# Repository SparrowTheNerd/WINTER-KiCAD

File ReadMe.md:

WINTER Revision 3.3 Board and Production Files. Legacy as of Aug 28, 2025

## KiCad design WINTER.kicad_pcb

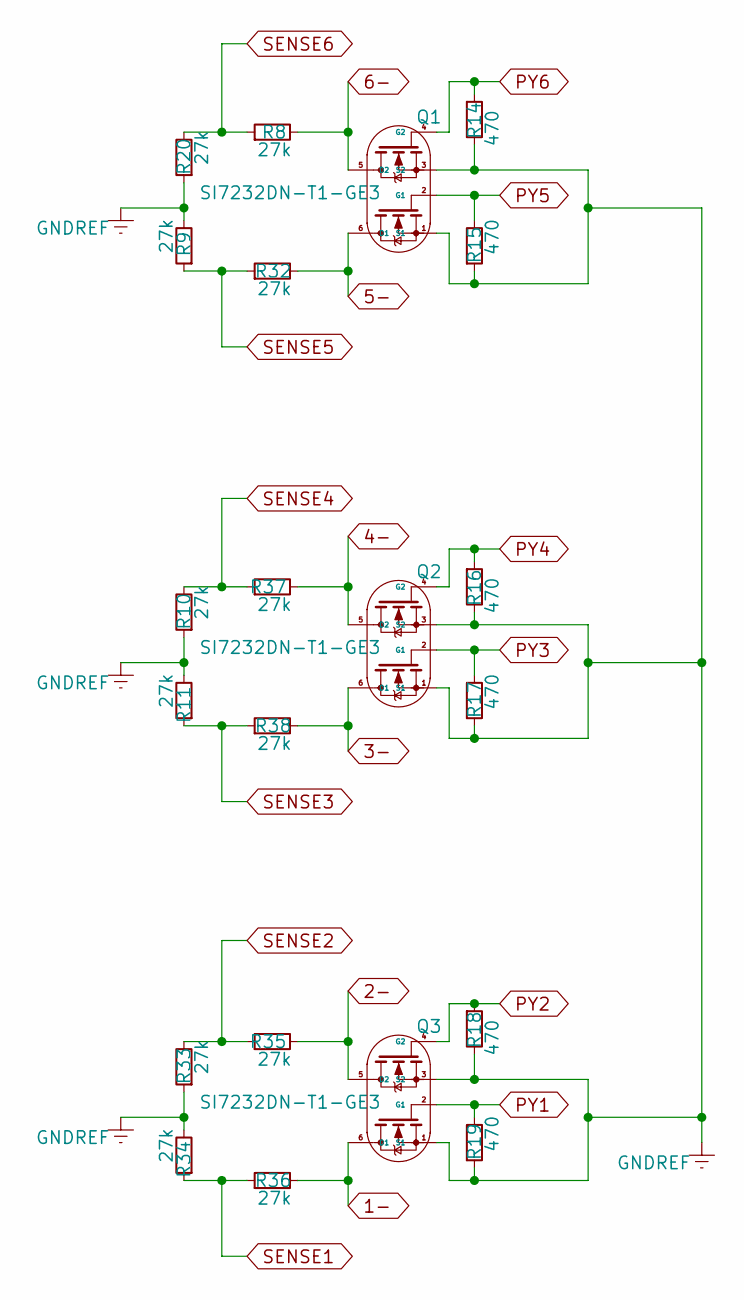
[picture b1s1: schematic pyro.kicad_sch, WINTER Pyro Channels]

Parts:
Q1, Q2, Q3: SI7232DN-T1-GE3; TRANS_SI7232DN-T1-GE3; LCSC C144854
R8, R32, R35, R36, R37, R38: 27k; R_0603_1608Metric; LCSC C22967
R9, R10, R11, R20, R33, R34: 27k; R_0603_1608Metric; LCSC C25803
R14, R15, R16, R17, R18, R19: 470; R_0603_1608Metric; LCSC C23179

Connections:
1-: Q3.6 (D1), R36.2; also elsewhere on the board
2-: Q3.5 (D2), R35.2; also elsewhere on the board
3-: Q2.6 (D1), R38.2; also elsewhere on the board
4-: Q2.5 (D2), R37.2; also elsewhere on the board
5-: Q1.6 (D1), R32.2; also elsewhere on the board
6-: Q1.5 (D2), R8.2; also elsewhere on the board
GNDREF: Q1.1 (S1), Q1.3 (S2), Q2.1 (S1), Q2.3 (S2), Q3.1 (S1), Q3.3 (S2), R9.2, R10.1, R11.2, R14.2, R15.1, R16.2, R17.1, R18.2, R19.1, R20.1, R33.1, R34.2; also elsewhere on the board
PY1: Q3.2 (G1), R19.2; also elsewhere on the board
PY2: Q3.4 (G2), R18.1; also elsewhere on the board
PY3: Q2.2 (G1), R17.2; also elsewhere on the board
PY4: Q2.4 (G2), R16.1; also elsewhere on the board
PY5: Q1.2 (G1), R15.2; also elsewhere on the board
PY6: Q1.4 (G2), R14.1; also elsewhere on the board
SENSE1: R34.1, R36.1; also elsewhere on the board
SENSE2: R33.2, R35.1; also elsewhere on the board
SENSE3: R11.1, R38.1; also elsewhere on the board
SENSE4: R10.2, R37.1; also elsewhere on the board
SENSE5: R9.1, R32.1; also elsewhere on the board
SENSE6: R8.1, R20.2; also elsewhere on the board

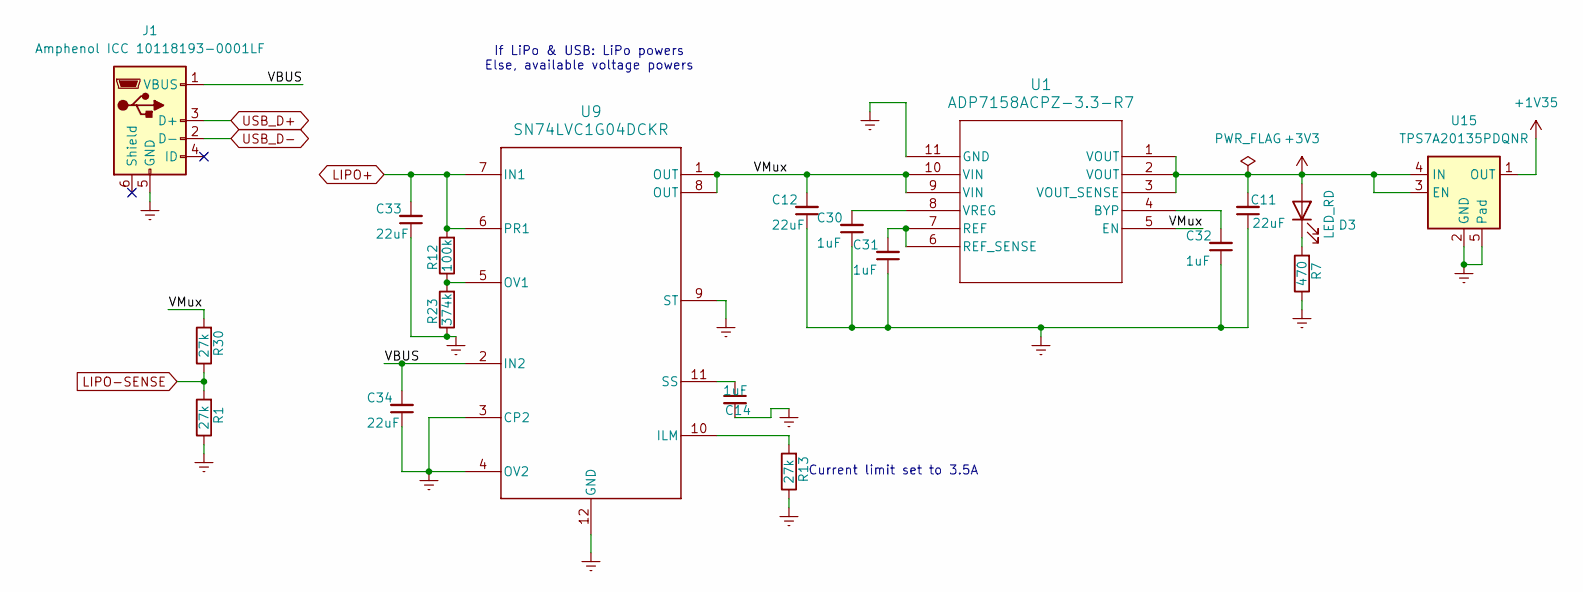
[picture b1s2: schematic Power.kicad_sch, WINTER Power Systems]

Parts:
C11, C12, C33, C34: 22uF; C_0603_1608Metric; LCSC C96446
C14: 1uF; C_0603_1608Metric; LCSC C1525
C30, C31, C32: 1uF; C_0603_1608Metric; LCSC C96446
D3: LED_RD; LED_0603_1608Metric; LCSC C2286
J1: Amphenol ICC 10118193-0001LF; USB_Micro-B_Amphenol_10118193-0001LF_Horizontal; LCSC C132562
R1, R13, R30: 27k; R_0603_1608Metric; LCSC C22967
R7: 470; R_0603_1608Metric; LCSC C23179
R12: 100k; R_0603_1608Metric; LCSC C23162
R23: 374k; R_0603_1608Metric
U1: ADP7158ACPZ-3.3-R7; CP-10-9_ADI
U9: SN74LVC1G04DCKR; RUX0012A
U15: TPS7A20135PDQNR; Texas_X2SON-4_1x1mm_P0.65mm

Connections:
+1V35: U15.1 (OUT); also elsewhere on the board
+3V3: C11.2, D3.2 (A), U1.1 (VOUT), U1.2 (VOUT), U1.3 (VOUT_SENSE), U15.3 (EN), U15.4 (IN); also elsewhere on the board
/Power/VBUS: C34.2, J1.1 (VBUS), U9.2 (IN2)
/Power/VMux: C12.2, R30.2, U1.5 (EN), U1.9 (VIN), U1.10 (VIN), U9.1 (OUT), U9.8 (OUT)
GNDREF: C11.1, C12.1, C14.2, C30.1, C31.1, C32.1, C33.1, C34.1, J1.5 (GND), R1.1, R7.1, R13.1, R23.1, U1.11 (GND), U9.3 (CP2), U9.4 (OV2), U9.9 (ST), U9.12 (GND), U15.2 (GND), U15.5 (Pad); also elsewhere on the board
LIPO+: C33.2, R12.2, U9.6 (PR1), U9.7 (IN1); also elsewhere on the board
LIPO-SENSE: R1.2, R30.1; also elsewhere on the board
unnamed: D3.1 (K), R7.2
unnamed: C32.2, U1.4 (BYP)
unnamed: C31.2, U1.6 (REF_SENSE), U1.7 (REF)
unnamed: C30.2, U1.8 (VREG)
unnamed: R13.2, U9.10 (ILM)
unnamed: R12.1, R23.2, U9.5 (OV1)
unnamed: C14.1, U9.11 (SS)
USB_D+: J1.3 (D+); also elsewhere on the board
USB_D-: J1.2 (D-); also elsewhere on the board

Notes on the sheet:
If LiPo & USB: LiPo powers Else, available voltage powers
Current limit set to 3.5A

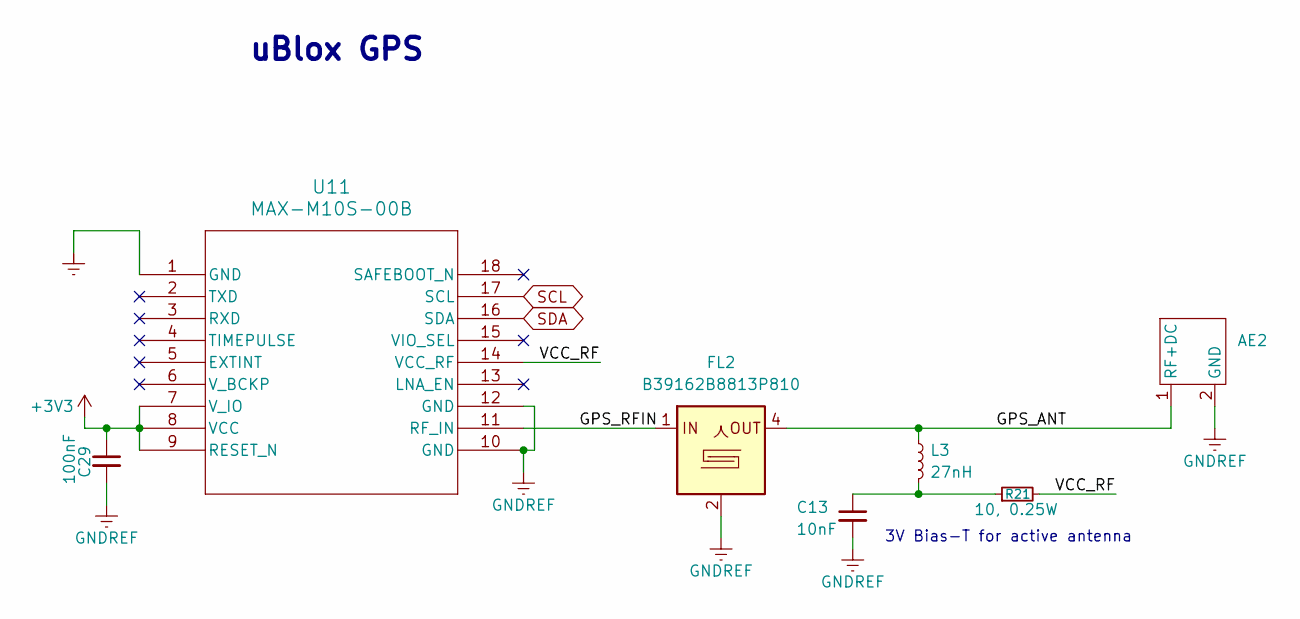
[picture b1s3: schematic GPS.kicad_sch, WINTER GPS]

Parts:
AE2: AP.10H.01
C13: 10nF; C_0603_1608Metric
C29: 100nF; C_0603_1608Metric; LCSC C1590
FL2: B39162B8813P810; Filter_1109-5_1.1x0.9mm
L3: 27nH; L_0402_1005Metric
R21: 10, 0.25W; R_0603_1608Metric
U11: MAX-M10S-00B; LCSC C4153167

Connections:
+3V3: C29.1, U11.7 (V_IO), U11.8 (VCC), U11.9 (RESET_N); also elsewhere on the board
/GPS/GPS_ANT: AE2.1 (RF+DC), FL2.4, L3.1
/GPS/GPS_RFIN: FL2.1, U11.11 (RF_IN)
/GPS/VCC_RF: R21.2, U11.14 (VCC_RF)
GNDREF: AE2.2 (GND), AE2.3 (GND), AE2.4 (GND), AE2.5 (GND), C13.2, C29.2, FL2.2, FL2.3, FL2.5, U11.1 (GND), U11.10 (GND), U11.12 (GND); also elsewhere on the board
unnamed: C13.1, L3.2, R21.1
SCL: U11.17 (SCL); also elsewhere on the board
SDA: U11.16 (SDA); also elsewhere on the board

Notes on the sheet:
uBlox GPS
3V Bias-T for active antenna

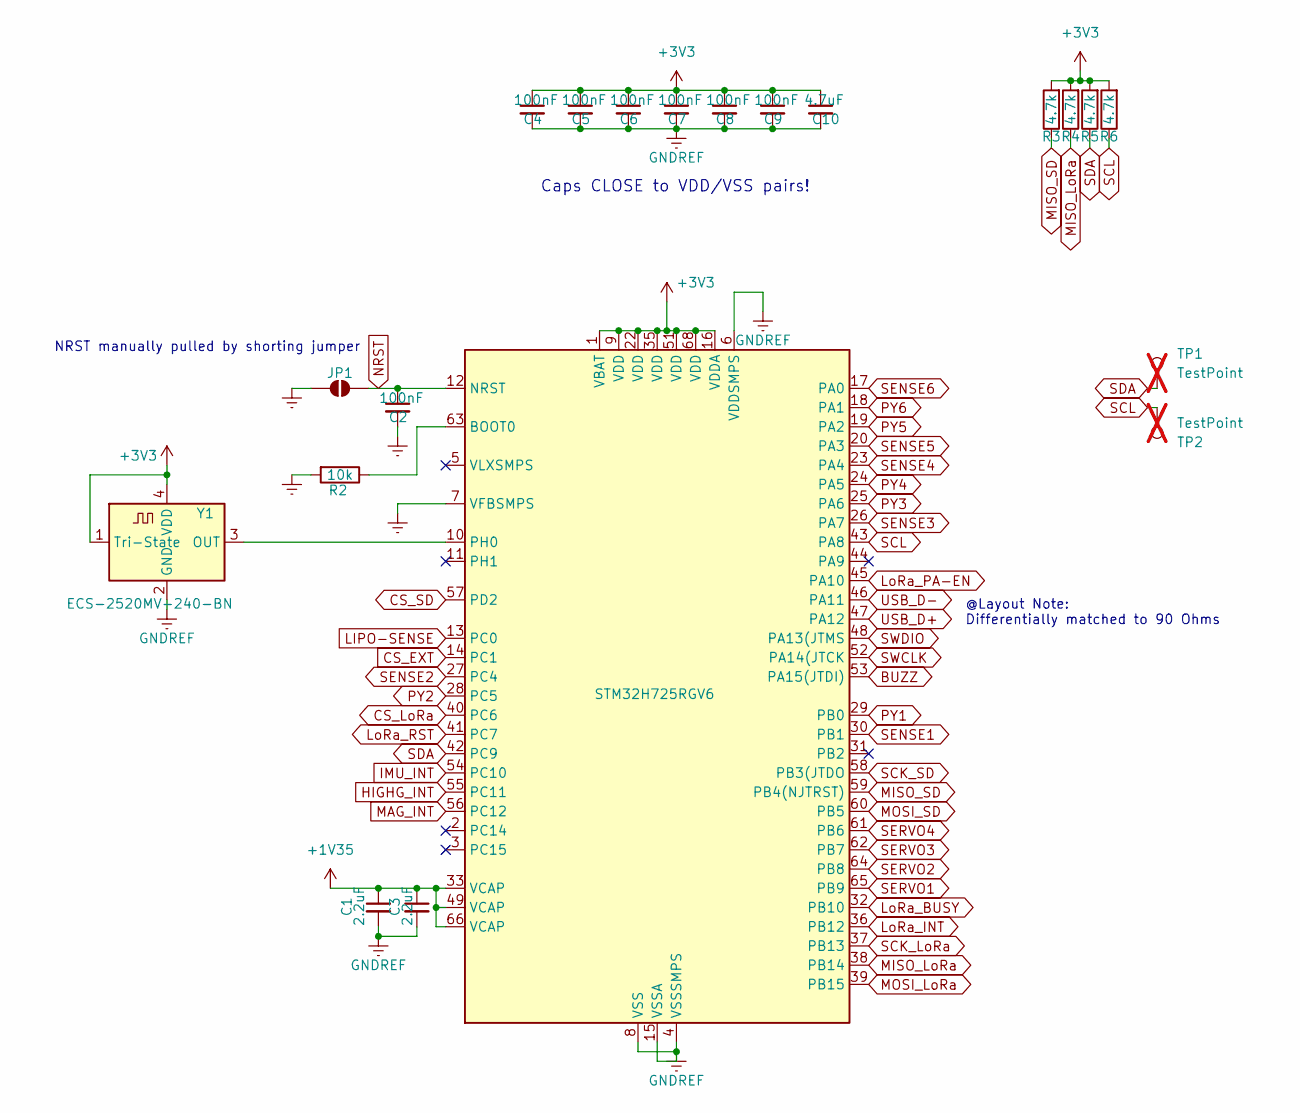
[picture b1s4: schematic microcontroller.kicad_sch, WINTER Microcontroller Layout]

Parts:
C1, C3: 2.2uF; C_0603_1608Metric; LCSC C23630
C2: 100nF; C_0603_1608Metric; LCSC C1590
C4, C5, C6, C7, C8, C9: 100nF; C_0603_1608Metric; LCSC C1525
C10: 4.7uF; C_0603_1608Metric; LCSC C23733
JP1: SolderJumper_2_Open; SolderJumper-2_P1.3mm_Open_RoundedPad1.0x1.5mm
R2: 10k; R_0603_1608Metric; LCSC C25804
R3, R4, R5, R6: 4.7k; R_0603_1608Metric; LCSC C23162
TP1, TP2: TestPoint; TestPoint_Pad_D1.0mm; LCSC DNP; not fitted
U6: STM32H725RGV6; QFN-68-1EP_8x8mm_P0.4mm_EP5.2x5.2mm; LCSC C5271079
Y1: ECS-2520MV-240-BN; Oscillator_SMD_ECS_2520MV-xxx-xx-4Pin_2.5x2.0mm; LCSC C437141

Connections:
+1V35: C1.1, C3.1, U6.33 (VCAP), U6.49 (VCAP), U6.66 (VCAP); also elsewhere on the board
+3V3: C4.1, C5.1, C6.1, C7.1, C8.1, C9.1, C10.1, R3.2, R4.2, R5.2, R6.2, U6.1 (VBAT), U6.9 (VDD), U6.16 (VDDA), U6.22 (VDD), U6.35 (VDD), U6.51 (VDD), U6.68 (VDD), Y1.1 (Tri-State), Y1.4 (VDD); also elsewhere on the board
BUZZ: U6.53 (PA15(JTDI)); also elsewhere on the board
CS_EXT: U6.14 (PC1); also elsewhere on the board
CS_LoRa: U6.40 (PC6); also elsewhere on the board
CS_SD: U6.57 (PD2); also elsewhere on the board
GNDREF: C1.2, C2.2, C3.2, C4.2, C5.2, C6.2, C7.2, C8.2, C9.2, C10.2, JP1.1 (A), R2.2, U6.4 (VSSSMPS), U6.6 (VDDSMPS), U6.7 (VFBSMPS), U6.8 (VSS), U6.15 (VSSA), U6.21 (VSS), U6.34 (VSS), U6.50 (VSS), U6.67 (VSS), U6.69 (VSS), Y1.2 (GND); also elsewhere on the board
HIGHG_INT: U6.55 (PC11); also elsewhere on the board
IMU_INT: U6.54 (PC10); also elsewhere on the board
LIPO-SENSE: U6.13 (PC0); also elsewhere on the board
LoRa_BUSY: U6.32 (PB10); also elsewhere on the board
LoRa_INT: U6.36 (PB12); also elsewhere on the board
LoRa_PA-EN: U6.45 (PA10); also elsewhere on the board
LoRa_RST: U6.41 (PC7); also elsewhere on the board
MAG_INT: U6.56 (PC12); also elsewhere on the board
MISO_LoRa: R4.1, U6.38 (PB14); also elsewhere on the board
MISO_SD: R3.1, U6.59 (PB4(NJTRST)); also elsewhere on the board
MOSI_LoRa: U6.39 (PB15); also elsewhere on the board
MOSI_SD: U6.60 (PB5); also elsewhere on the board
NRST: C2.1, JP1.2 (B), U6.12 (NRST); also elsewhere on the board
unnamed: R2.1, U6.63 (BOOT0)
unnamed: U6.10 (PH0), Y1.3 (OUT)
PY1: U6.29 (PB0); also elsewhere on the board
PY2: U6.28 (PC5); also elsewhere on the board
PY3: U6.25 (PA6); also elsewhere on the board
PY4: U6.24 (PA5); also elsewhere on the board
PY5: U6.19 (PA2); also elsewhere on the board
PY6: U6.18 (PA1); also elsewhere on the board
SCK_LoRa: U6.37 (PB13); also elsewhere on the board
SCK_SD: U6.58 (PB3(JTDO); also elsewhere on the board
SCL: R6.1, TP2.1, U6.43 (PA8); also elsewhere on the board
SDA: R5.1, TP1.1, U6.42 (PC9); also elsewhere on the board
SENSE1: U6.30 (PB1); also elsewhere on the board
SENSE2: U6.27 (PC4); also elsewhere on the board
SENSE3: U6.26 (PA7); also elsewhere on the board
SENSE4: U6.23 (PA4); also elsewhere on the board
SENSE5: U6.20 (PA3); also elsewhere on the board
SENSE6: U6.17 (PA0); also elsewhere on the board
SERVO1: U6.65 (PB9); also elsewhere on the board
SERVO2: U6.64 (PB8); also elsewhere on the board
SERVO3: U6.62 (PB7); also elsewhere on the board
SERVO4: U6.61 (PB6); also elsewhere on the board
SWCLK: U6.52 (PA14(JTCK); also elsewhere on the board
SWDIO: U6.48 (PA13(JTMS); also elsewhere on the board
USB_D+: U6.47 (PA12); also elsewhere on the board
USB_D-: U6.46 (PA11); also elsewhere on the board

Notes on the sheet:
Caps CLOSE to VDD/VSS pairs!
NRST manually pulled by shorting jumper
@Layout Note: Differentially matched to 90 Ohms

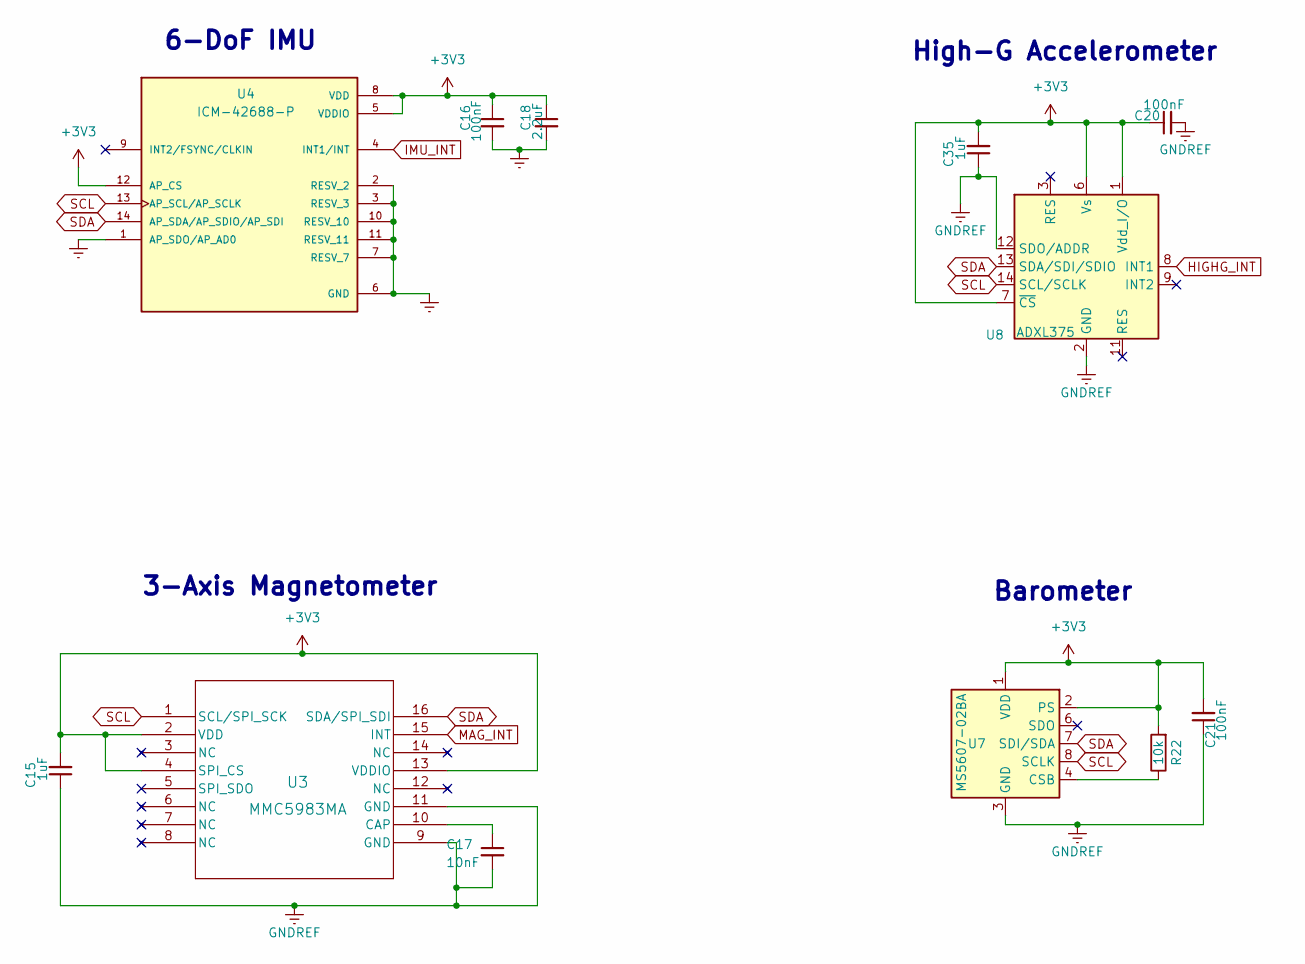
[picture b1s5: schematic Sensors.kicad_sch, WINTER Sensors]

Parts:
C15, C35: 1uF; C_0603_1608Metric
C16, C20, C21: 100nF; C_0603_1608Metric; LCSC C1525
C17: 10nF; C_0603_1608Metric
C18: 2.2uF; C_0603_1608Metric; LCSC C23630
R22: 10k; R_0603_1608Metric; LCSC C25804
U3: MMC5983MA; MMC5983MA_MEM; LCSC C404329
U4: ICM-42688-P; PQFN50P300X250X97-14N; PARTREV 1.2; LCSC C1850418
U7: MS5607-02BA; LGA-8_3x5mm_P1.25mm; LCSC C97627
U8: ADXL375; LGA-14_3x5mm_P0.8mm_LayoutBorder1x6y; LCSC C481898

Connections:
+3V3: C15.2, C16.1, C18.1, C20.1, C21.2, C35.2, R22.2, U3.2 (VDD), U3.4 (SPI_CS), U3.13 (VDDIO), U4.5 (VDDIO), U4.8 (VDD), U4.12 (AP_CS), U7.1 (VDD), U7.2 (PS), U8.1 (Vdd_I/O), U8.6 (Vs), U8.7 (~CS); also elsewhere on the board
GNDREF: C15.1, C16.2, C17.2, C18.2, C20.2, C21.1, C35.1, U3.9 (GND), U3.11 (GND), U4.1 (AP_SDO/AP_AD0), U4.2 (RESV_2), U4.3 (RESV_3), U4.6 (GND), U4.7 (RESV_7), U4.10 (RESV_10), U4.11 (RESV_11), U7.3 (GND), U8.2 (GND), U8.4 (GND), U8.5 (GND), U8.12 (SDO/ADDR); also elsewhere on the board
HIGHG_INT: U8.8 (INT1); also elsewhere on the board
IMU_INT: U4.4 (INT1/INT); also elsewhere on the board
MAG_INT: U3.15 (INT); also elsewhere on the board
unnamed: R22.1, U7.4 (CSB), U7.5 (CSB)
unnamed: C17.1, U3.10 (CAP)
SCL: U3.1 (SCL/SPI_SCK), U4.13 (AP_SCL/AP_SCLK), U7.8 (SCLK), U8.14 (SCL/SCLK); also elsewhere on the board
SDA: U3.16 (SDA/SPI_SDI), U4.14 (AP_SDA/AP_SDIO/AP_SDI), U7.7 (SDI/SDA), U8.13 (SDA/SDI/SDIO); also elsewhere on the board

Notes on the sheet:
3-Axis Magnetometer
Barometer
6-DoF IMU
High-G Accelerometer

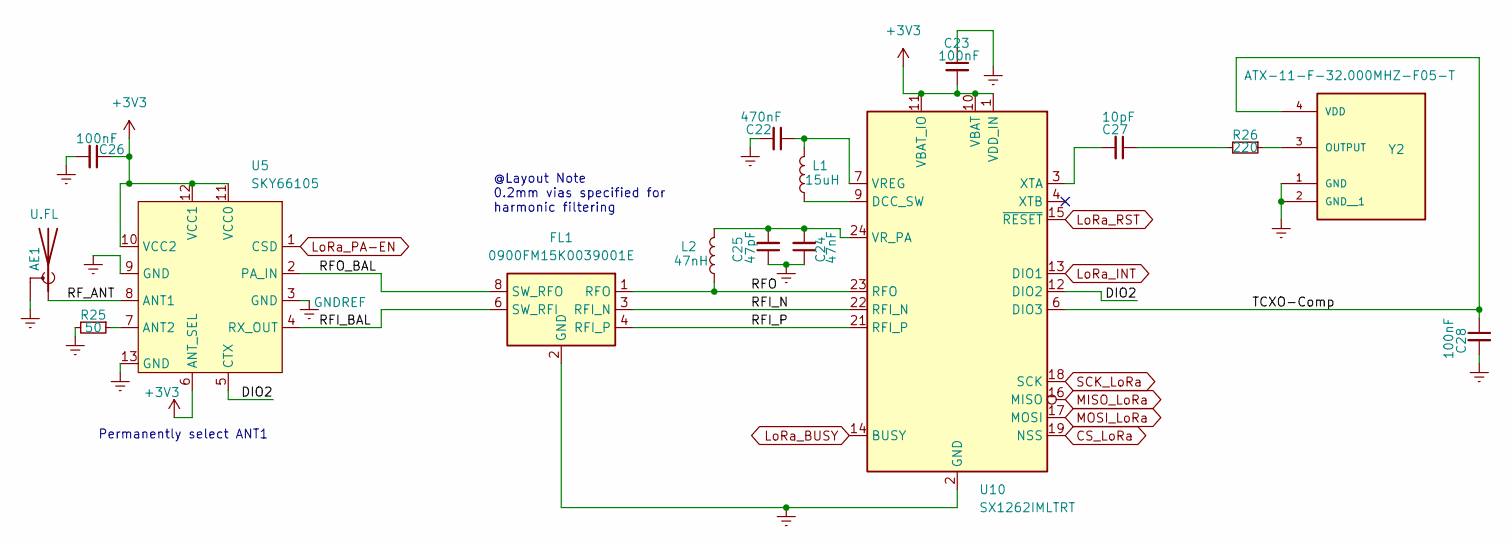
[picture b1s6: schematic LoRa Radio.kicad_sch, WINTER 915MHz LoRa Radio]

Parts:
AE1: U.FL; U.FL_Molex_MCRF_73412-0110_Vertical; LCSC C434806
C22: 470nF; C_0603_1608Metric; LCSC C1623
C23, C26, C28: 100nF; C_0603_1608Metric; LCSC C1590
C24: 47nF; C_0201_0603Metric; LCSC C85925
C25: 47pF; C_0201_0603Metric; LCSC C85908
C27: 10pF; C_0603_1608Metric; LCSC C32949
FL1: 0900FM15K0039001E; Balun_Johanson_0900FM15K0039; LCSC C1513363
L1: 15uH; L_0805_2012Metric; LCSC C383402
L2: 47nH; L_0402_1005Metric; LCSC C76776
R25: 50; R_0402_1005Metric; LCSC C227387
R26: 220; R_0603_1608Metric; LCSC C25091
U5: SKY66105; SKY66105-11; LCSC C2654446
U10: SX1262IMLTRT; QFN-24-1EP_4x4mm_P0.5mm_EP2.6x2.6mm; LCSC C191341
Y2: ATX-11-F-32.000MHZ-F05-T; OSC_ATX-11-F-32.000MHZ-F05-T; PARTREV 11-11-20; LCSC C5978624

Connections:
+3V3: C23.2, C26.1, U5.6 (ANT_SEL), U5.10 (VCC2), U5.11 (VCC0), U5.12 (VCC1), U10.1 (VDD_IN), U10.10 (VBAT), U10.11 (VBAT_IO); also elsewhere on the board
/LoRa Radio/DIO2: U5.5 (CTX), U10.12 (DIO2)
/LoRa Radio/RFI_BAL: FL1.6 (SW_RFI), U5.4 (RX_OUT)
/LoRa Radio/RFI_N: FL1.3 (RFI_N), U10.22 (RFI_N)
/LoRa Radio/RFI_P: FL1.4 (RFI_P), U10.21 (RFI_P)
/LoRa Radio/RFO: FL1.1 (RFO), L2.1, U10.23 (RFO)
/LoRa Radio/RFO_BAL: FL1.8 (SW_RFO), U5.2 (PA_IN)
/LoRa Radio/RF_ANT: AE1.1 (A), U5.8 (ANT1)
/LoRa Radio/TCXO-Comp: C28.1, U10.6 (DIO3), Y2.4 (VDD)
CS_LoRa: U10.19 (NSS); also elsewhere on the board
GNDREF: AE1.2 (Shield), C22.2, C23.1, C24.1, C25.1, C26.2, C28.2, FL1.2 (GND), FL1.5 (GND), FL1.7 (GND), FL1.9 (GND), FL1.10 (GND), R25.2, U5.3 (GND), U5.9 (GND), U5.13 (GND), U10.2 (GND), U10.5 (GND), U10.8 (GND), U10.20 (GND), U10.25 (GND), Y2.1 (GND), Y2.2 (GND__1); also elsewhere on the board
LoRa_BUSY: U10.14 (BUSY); also elsewhere on the board
LoRa_INT: U10.13 (DIO1); also elsewhere on the board
LoRa_PA-EN: U5.1 (CSD); also elsewhere on the board
LoRa_RST: U10.15 (~RESET); also elsewhere on the board
MISO_LoRa: U10.16 (MISO); also elsewhere on the board
MOSI_LoRa: U10.17 (MOSI); also elsewhere on the board
unnamed: C27.1, R26.2
unnamed: R25.1, U5.7 (ANT2)
unnamed: L1.1, U10.9 (DCC_SW)
unnamed: C22.1, L1.2, U10.7 (VREG)
unnamed: C24.2, C25.2, L2.2, U10.24 (VR_PA)
unnamed: C27.2, U10.3 (XTA)
unnamed: R26.1, Y2.3 (OUTPUT)
SCK_LoRa: U10.18 (SCK); also elsewhere on the board

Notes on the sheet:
Permanently select ANT1
@Layout Note 0.2mm vias specified for harmonic filtering

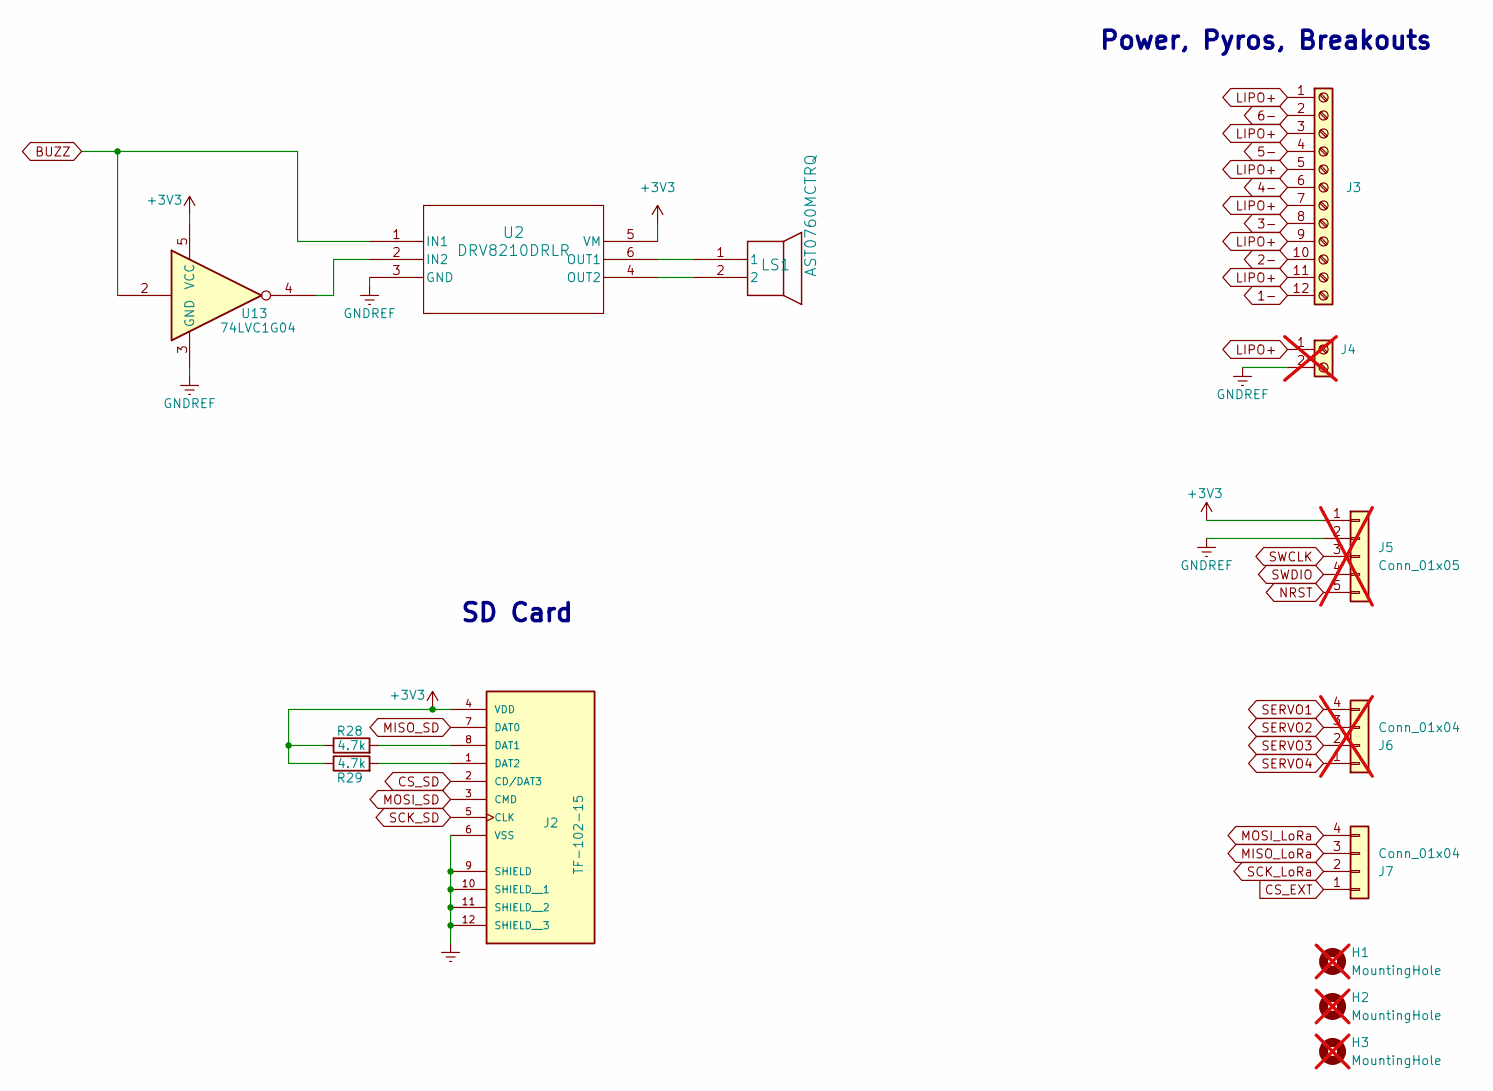
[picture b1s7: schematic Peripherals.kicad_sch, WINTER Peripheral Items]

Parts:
H1, H2, H3: MountingHole; MountingHole_2.2mm_M2_ISO7380_Pad_TopOnly; LCSC DNP; not fitted
J2: TF-102-15; microSD_GCT_MEM2067-02-180-00; LCSC C266609
J3: Screw_Terminal_01x12; TerminalBlock_Phoenix_MPT-0,5-12-2.54_1x12_P2.54mm_Horizont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; LCSC DNP
J4: Screw_Terminal_01x02; SolderWire-0.75sqmm_1x02_P7mm_D1.25mm_OD3.5mm; LCSC DNP; not fitted
J5: Conn_01x05; PinHeader_1x05_P2.54mm_Vertical; LCSC DNP; not fitted
J6: Conn_01x04; PinHeader_1x04_P2.54mm_Vertical; LCSC DNP; not fitted
J7: Conn_01x04; PinHeader_1x04_P2.54mm_Vertical; LCSC DNP
LS1: AST0760MCTRQ; AST0760_MAL; LCSC C5949284
R28, R29: 4.7k; R_0603_1608Metric; LCSC C23162
U2: DRV8210DRLR; SOT_210DRLR_TEX; LCSC C3681297
U13: 74LVC1G04; Texas_R-PDSO-G5_DCK-5; LCSC C8207

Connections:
1-: J3.12; also elsewhere on the board
2-: J3.10; also elsewhere on the board
3-: J3.8; also elsewhere on the board
4-: J3.6; also elsewhere on the board
5-: J3.4; also elsewhere on the board
6-: J3.2; also elsewhere on the board
+3V3: J2.4 (VDD), J5.1, R28.1, R29.1, U2.5 (VM), U13.5 (VCC); also elsewhere on the board
BUZZ: U2.1 (IN1), U13.2; also elsewhere on the board
CS_EXT: J7.1; also elsewhere on the board
CS_SD: J2.2 (CD/DAT3); also elsewhere on the board
GNDREF: J2.6 (VSS), J2.9 (SHIELD), J2.10 (SHIELD__1), J2.11 (SHIELD__2), J2.12 (SHIELD__3), J4.2, J5.2, U2.3 (GND), U13.3 (GND); also elsewhere on the board
LIPO+: J3.1, J3.3, J3.5, J3.7, J3.9, J3.11, J4.1; also elsewhere on the board
MISO_LoRa: J7.3; also elsewhere on the board
MISO_SD: J2.7 (DAT0); also elsewhere on the board
MOSI_LoRa: J7.4; also elsewhere on the board
MOSI_SD: J2.3 (CMD); also elsewhere on the board
NRST: J5.5; also elsewhere on the board
unnamed: J2.8 (DAT1), R28.2
unnamed: J2.1 (DAT2), R29.2
unnamed: U2.2 (IN2), U13.4
unnamed: LS1.1, U2.6 (OUT1)
unnamed: LS1.2, U2.4 (OUT2)
SCK_LoRa: J7.2; also elsewhere on the board
SCK_SD: J2.5 (CLK); also elsewhere on the board
SERVO1: J6.4; also elsewhere on the board
SERVO2: J6.3; also elsewhere on the board
SERVO3: J6.2; also elsewhere on the board
SERVO4: J6.1; also elsewhere on the board
SWCLK: J5.3; also elsewhere on the board
SWDIO: J5.4; also elsewhere on the board

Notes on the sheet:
SD Card
Power, Pyros, Breakouts

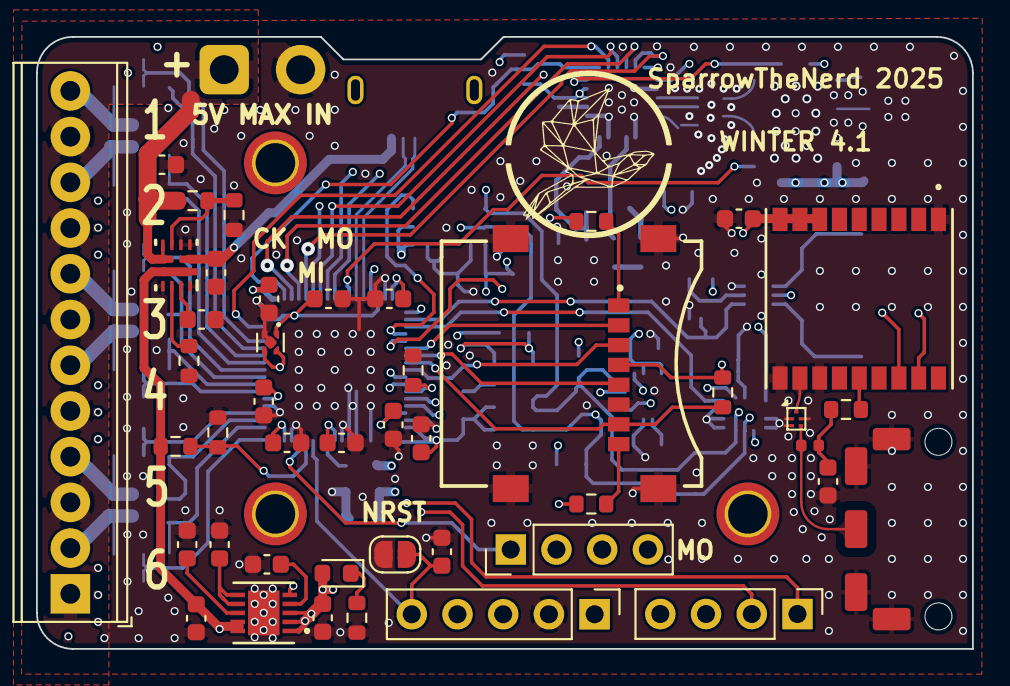
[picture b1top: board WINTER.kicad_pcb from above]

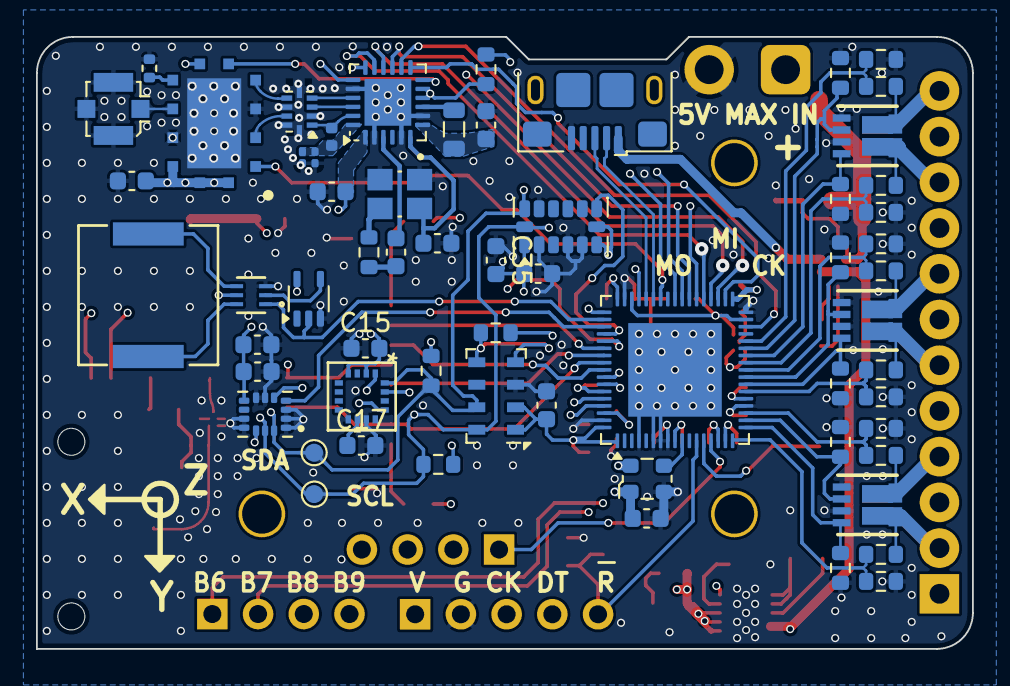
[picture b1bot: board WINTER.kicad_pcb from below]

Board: 6 copper layers, 52.0 x 34.0 mm, 109 parts (61 on the bottom side), 88 nets.
